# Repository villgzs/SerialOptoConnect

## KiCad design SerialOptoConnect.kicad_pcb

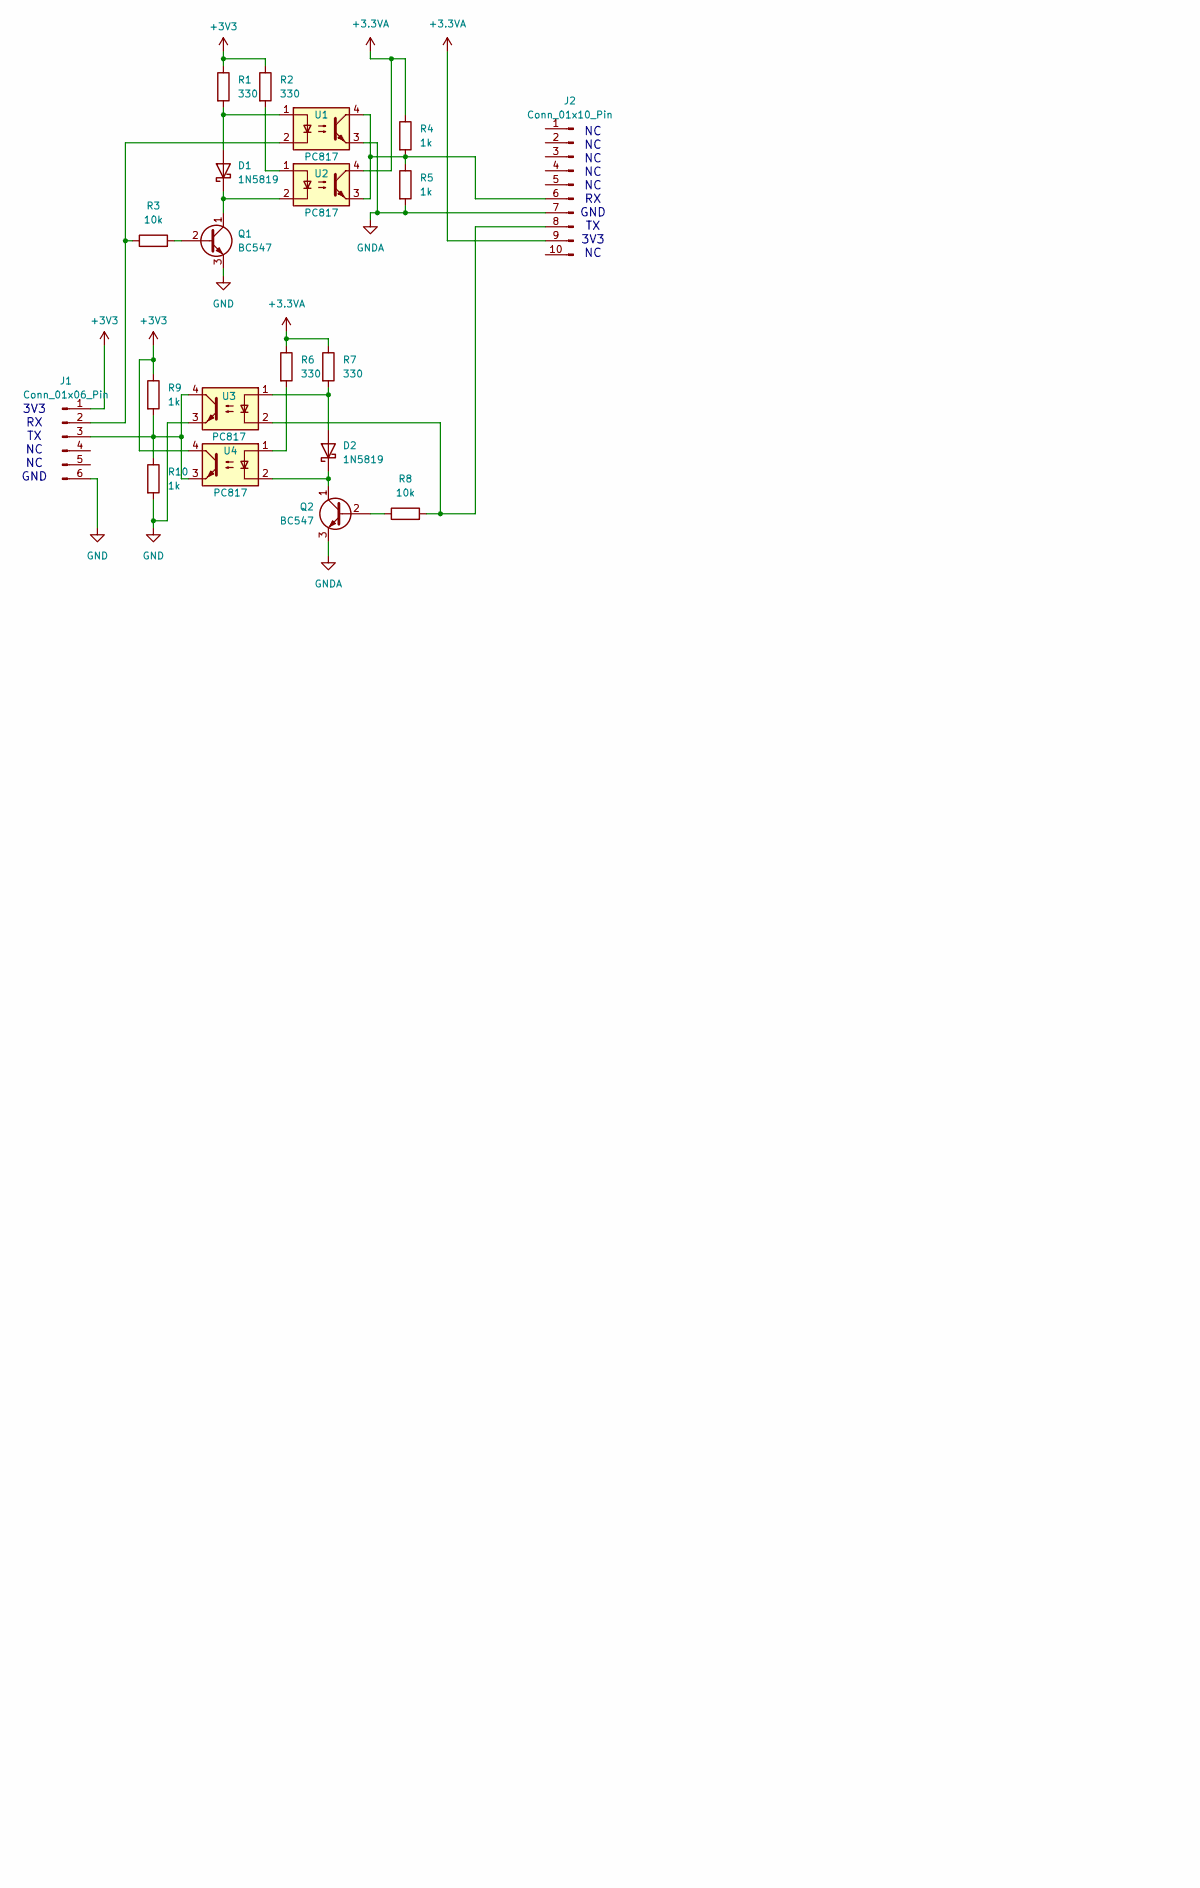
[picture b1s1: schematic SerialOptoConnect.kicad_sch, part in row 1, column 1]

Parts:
D1, D2: 1N5819; D_DO-34_SOD68_P7.62mm_Horizontal
J1: Conn_01x06_Pin; PinHeader_1x06_P2.54mm_Vertical
J2: Conn_01x10_Pin; PinHeader_1x10_P2.54mm_Vertical
Q1, Q2: BC547; TO-92L_Inline_Wide
R1, R2, R6, R7: 330; R_Axial_DIN0204_L3.6mm_D1.6mm_P5.08mm_Horizontal
R3, R8: 10k; R_Axial_DIN0204_L3.6mm_D1.6mm_P5.08mm_Horizontal
R4, R5, R9, R10: 1k; R_Axial_DIN0204_L3.6mm_D1.6mm_P5.08mm_Horizontal
U1, U2, U3, U4: PC817; DIP-4_W7.62mm

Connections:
+3.3VA: J2.9, R4.1, R6.1, R7.1, U2.4
+3V3: J1.1, R1.1, R2.1, R9.1, U4.4
GND: J1.6, Q1.3 (E), R10.2, U3.3
GNDA: J2.7, Q2.3 (E), R5.2, U1.3
unnamed: D1.2 (A), R1.2, U1.1
unnamed: D1.1 (K), Q1.1 (C), U2.2
unnamed: D2.2 (A), R7.2, U3.1
unnamed: D2.1 (K), Q2.1 (C), U4.2
unnamed: J1.2, R3.1, U1.2
unnamed: J1.3, R9.2, R10.1, U3.4, U4.3
unnamed: J2.6, R4.2, R5.1, U1.4, U2.3
unnamed: J2.8, R8.2, U3.2
unnamed: Q1.2 (B), R3.2
unnamed: Q2.2 (B), R8.1
unnamed: R2.2, U2.1
unnamed: R6.2, U4.1

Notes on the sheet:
3V3 RX TX NC NC GND
NC NC NC NC NC RX GND TX 3V3 NC

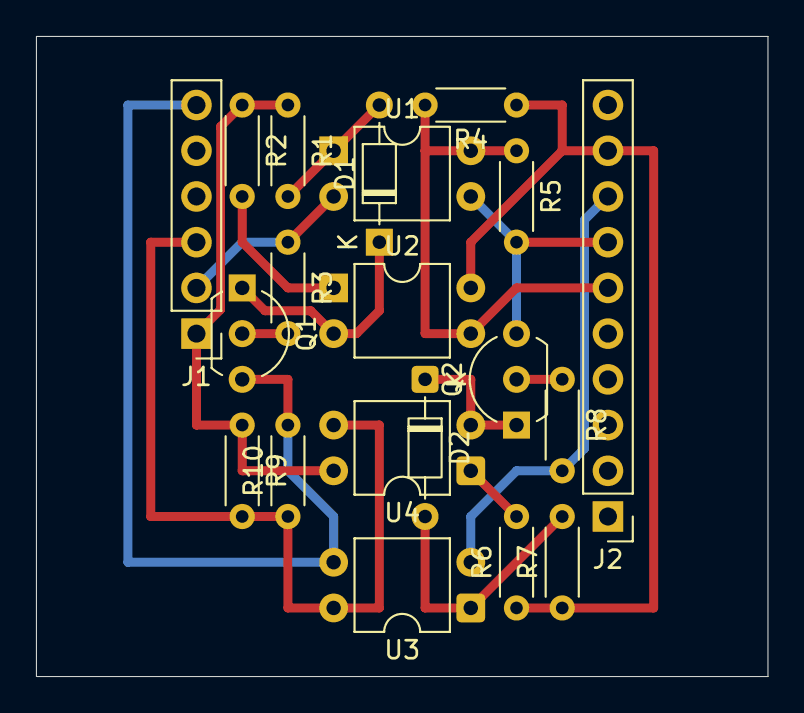
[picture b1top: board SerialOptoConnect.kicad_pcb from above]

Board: 2 copper layers, 40.6 x 35.6 mm, 20 parts (0 on the bottom side), 16 nets.

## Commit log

2026-03-10 initial version
2026-03-10 Falstad simulation
2026-03-10 Removing some files
2026-03-10 cleaning
2026-03-11 some small alignments
